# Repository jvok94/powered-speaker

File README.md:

# Connector Pin-outs

## SK1 (Power)

1. Ground
2. 24V AC 3A

## SK2 (Audio Input)

1. Left
2. Right
3. Ground

## SK3 (Volume Potentiometer)

1. Element (right contact)
2. Wiper
3. Element (left contact)

## SK4 (Speaker)

1. Live
2. Ground

## SK5 (LED)

1. Anode
2. Cathode

# Notes

* 2-pin connectors are Farnell order code 9632670 (https://uk.farnell.com/imo-precision-controls/20-101m-2/terminal-block-wire-to-brd-2pos/dp/9632670).
* 3-pin connectors are Farnell order code 9632689 (https://uk.farnell.com/imo-precision-controls/20-101m-3/terminal-block-wire-to-brd-3pos/dp/9632689).
* Power supply should be 24V AC (not DC), capable of at least 3A.
* Fuseholder F1 should be fitted with 3A time-lag fuse.
* To reduce hum, use shielded cable for input and potentiometer connections.

# Heatsinking

Q11 and Q12 should be attached to a heatsink with a maximum thermal resistance of 5K/W (lower is better). The tabs of the TO-220 packages are live, and so must be isolated from the heatsink using thermal pads. Mica or kapton work best, but SilPads are also acceptable. Either use nylon screws, or insulate the screws using suitable plastic bushings. A suitable kit containing both mica pads and bushings is available from Farnell, order code 520214 (https://uk.farnell.com/multicomp/mk3306/insulating-kit-mica-to-220/dp/520214). If using mica or kapton pads, coat them on both sides with a thin layer of thermal grease. Don't spread it too thick - you only need a very thin coating. Thermal grease is not required when using SilPads.

For everything you could possibly want to know about heatsinks (and more), a good read is http://sound.whsites.net/heatsinks.htm. Remember that when it comes to heatsinks, bigger is always better, and results in a cooler-running, more reliable amplifier

For optimum thermal stability, Q7 and Q9 should be in direct thermal contact with each other. Coat the back of one of the transistors with thermal grease, then use a cable tie around both transistor packages to hold them together. Doing the same with Q1 and Q2 will help to stop the DC offset from drifting with temperature.

# Assembly procedure

Solder all components to the PCB except for Q11 and Q12. You will need to fabricate some mounting to hold the PCB and heatsink together - do not rely on the transistor leads, as they or the solder joints will break. Once the PCB and heatsink are mounted, fit Q11 and Q12 to the board and bolt them to the heatsink. Solder the transistor leads last, after the packages have been mounted. This will reduce tension on the solder joints and prevent them from breaking. Using an ohmmeter, check to make sure there is no short circuit between the tabs of Q11 or Q12 and heatsink.

Adjust VR1 for to its minimum setting (1.2k resistance between base and emitter of Q7 - check this with a multimeter). Apply power but do not connect the audio input or speaker yet. Connect a voltmeter between the collectors of Q11 and Q12, then adjust VR1 until you measure 33mV - this corresponds to a quiescent current of 35mA. Leave the amplifier powered up for 30 minutes for the heatsink temperature to stabilise. After doing this, you are likely to find that the voltage has changed, so adjust VR1 again to bring it back to 33mV. Repeat this several times until the reading is stable. While doing this, monitor the heatsink temperature to ensure the amplifier does not overheat. The heatsink may get lukewarm but should not be hot.

Now connect the voltmeter across the speaker output. You may measure a small DC offset, but this should be less than 100mV. Anything larger than this indicates a construction error. Also check that there is no DC voltage on the input connector, to avoid damage to your audio source. Connect a speaker and audio source and listen to make sure that there is no distortion.

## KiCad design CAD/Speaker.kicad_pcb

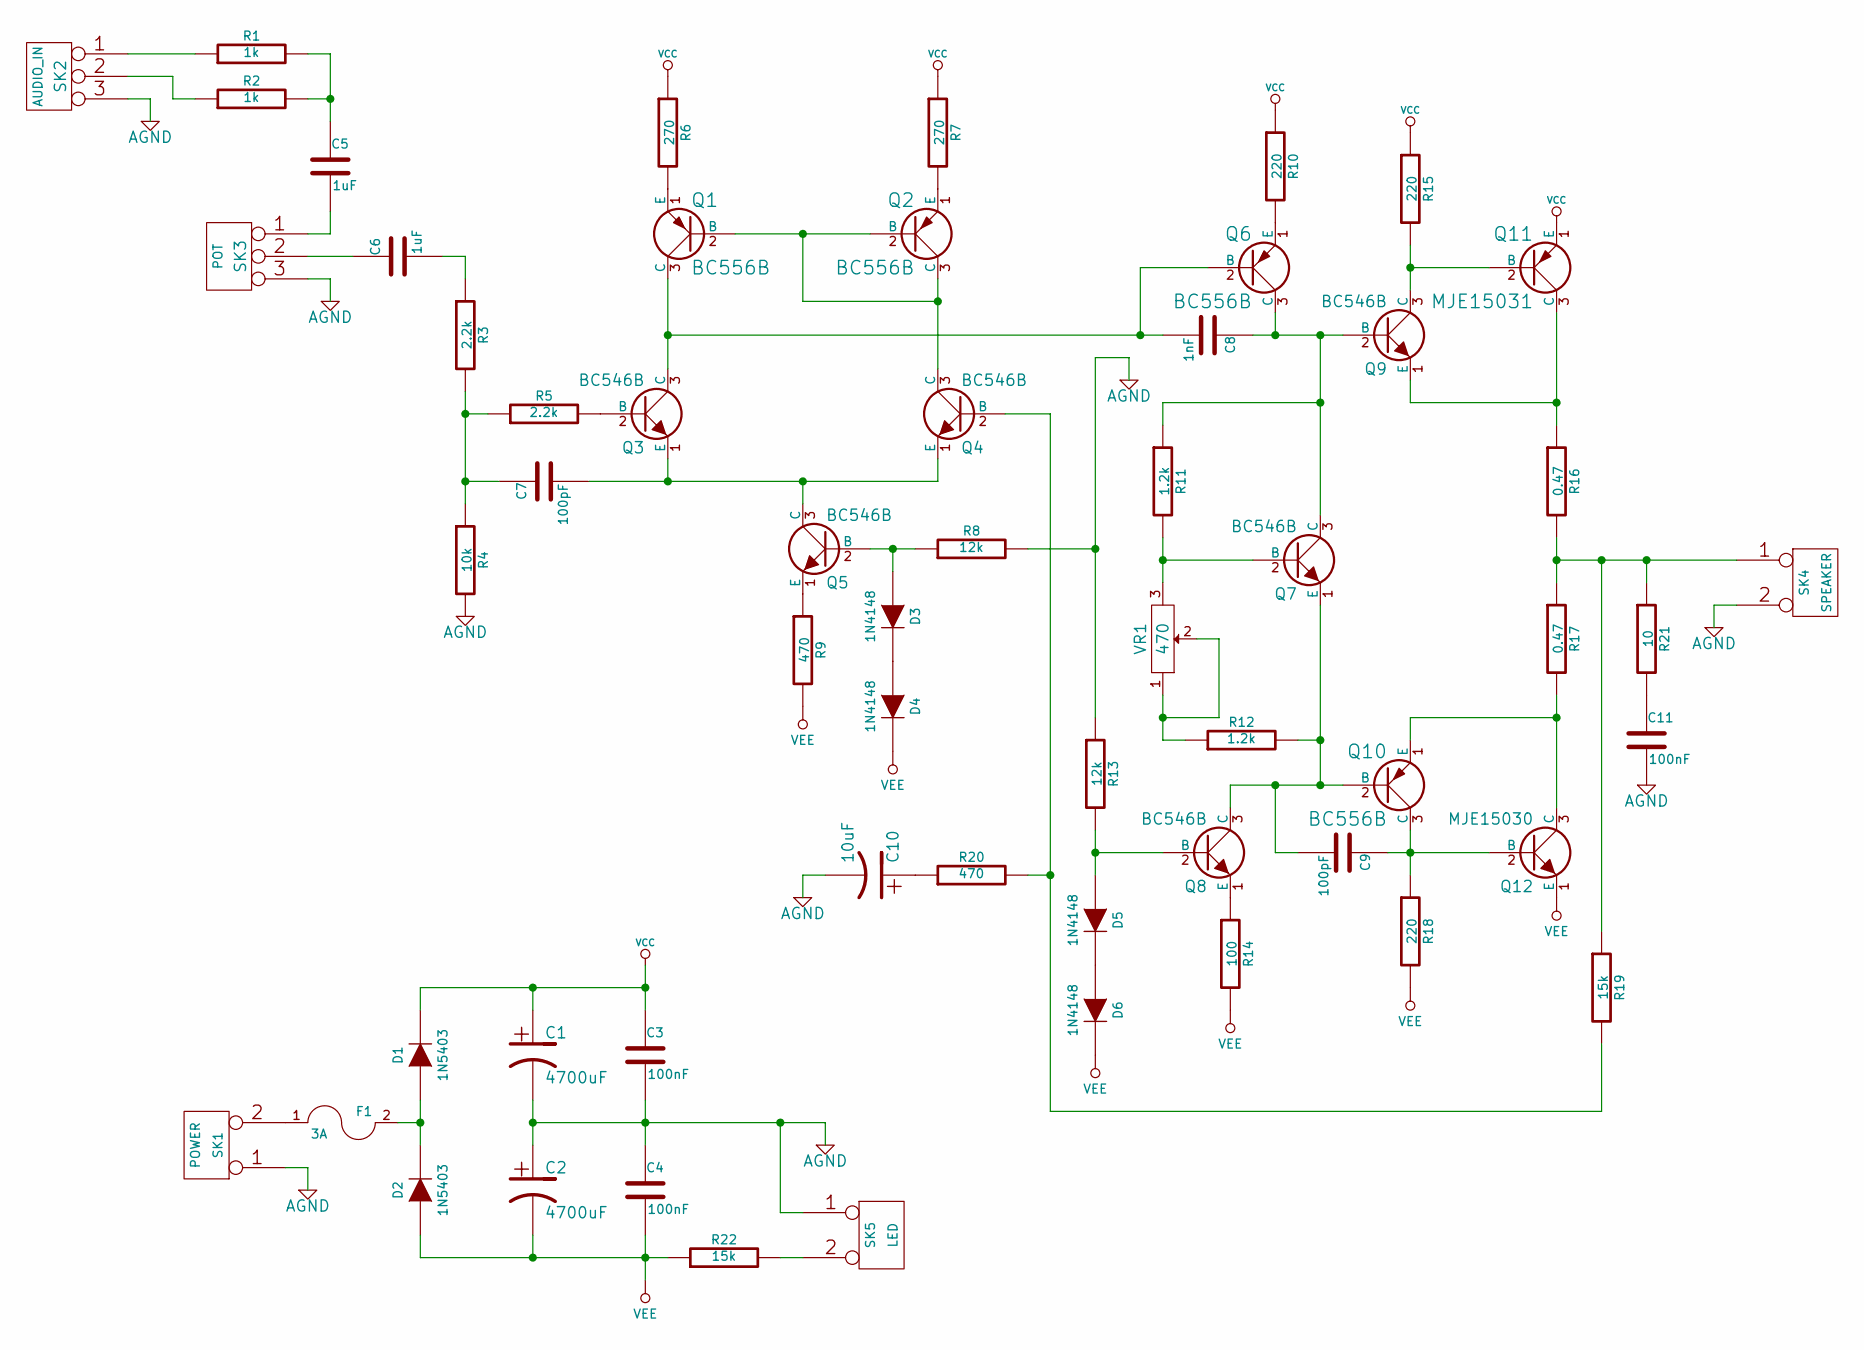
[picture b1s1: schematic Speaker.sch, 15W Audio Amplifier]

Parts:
C1, C2: 4700uF
C3, C4, C11: 100nF
C5, C6: 1uF
C7, C9: 100pF
C8: 1nF
C10: 10uF
D1, D2: 1N5403
D3, D4, D5, D6: 1N4148
F1: 3A
Q1, Q2, Q6, Q10: BC556B
Q3, Q4, Q5, Q7, Q8, Q9: BC546B
Q11: MJE15031
Q12: MJE15030
R1, R2: 1k
R3, R5: 2.2k
R4: 10k
R6, R7: 270
R8, R13: 12k
R9, R20: 470
R10, R15, R18: 220
R11, R12: 1.2k
R14: 100
R16, R17: 0.47
R19, R22: 15k
R21: 10
SK1: POWER
SK2: AUDIO_IN
SK3: POT
SK4: SPEAKER
SK5: LED
VR1: 470

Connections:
AGND: C1.2, C2.1, C3.2, C4.1, C10.2, C11.2, R4.2, R8.2, R13.1, SK1.1, SK2.3, SK3.3, SK4.2 (PM), SK5.1
unnamed: C7.1, R3.2, R4.1, R5.1
unnamed: C6.2, R3.1
unnamed: D5.2 (K), D6.1 (A)
unnamed: Q10.1 (E), Q12.3 (C), R17.2
unnamed: C9.1, Q10.3 (C), Q12.2 (B), R18.1
unnamed: Q9.1 (E), Q11.3 (C), R16.1
unnamed: C8.1, Q6.3 (C), Q7.3 (C), Q9.2 (B), R11.1
unnamed: Q7.2 (B), R11.2, VR1.3
unnamed: R1.1, SK2.1
unnamed: C5.1, R1.2, R2.2
unnamed: R2.1, SK2.2 (PM)
unnamed: Q9.3 (C), Q11.2 (B), R15.2
unnamed: C5.2, SK3.1
unnamed: D1.1 (A), D2.2 (K), F1.2
unnamed: F1.1, SK1.2 (PM)
unnamed: C6.1, SK3.2 (PM)
unnamed: R22.2, SK5.2 (PM)
unnamed: R12.1, VR1.1, VR1.2
unnamed: Q2.1 (E), R7.2
unnamed: Q1.1 (E), R6.2
unnamed: C8.2, Q1.3 (C), Q3.3 (C), Q6.2 (B)
unnamed: Q3.2 (B), R5.2
unnamed: D3.2 (K), D4.1 (A)
unnamed: C10.1, R20.1
unnamed: D3.1 (A), Q5.2 (B), R8.1
unnamed: Q5.1 (E), R9.1
unnamed: C7.2, Q3.1 (E), Q4.1 (E), Q5.3 (C)
unnamed: Q6.1 (E), R10.2
unnamed: C9.2, Q7.1 (E), Q8.3 (C), Q10.2 (B), R12.2
unnamed: Q8.1 (E), R14.1
unnamed: D5.1 (A), Q8.2 (B), R13.2
unnamed: R16.2, R17.1, R19.1, R21.1, SK4.1
unnamed: Q4.2 (B), R19.2, R20.2
unnamed: Q1.2 (B), Q2.2 (B), Q2.3 (C), Q4.3 (C)
unnamed: C11.1, R21.2
VCC: C1.1, C3.1, D1.2 (K), Q11.1 (E), R6.1, R7.1, R10.1, R15.1
VEE: C2.2, C4.2, D2.1 (A), D4.2 (K), D6.2 (K), Q12.1 (E), R9.2, R14.2, R18.2, R22.1

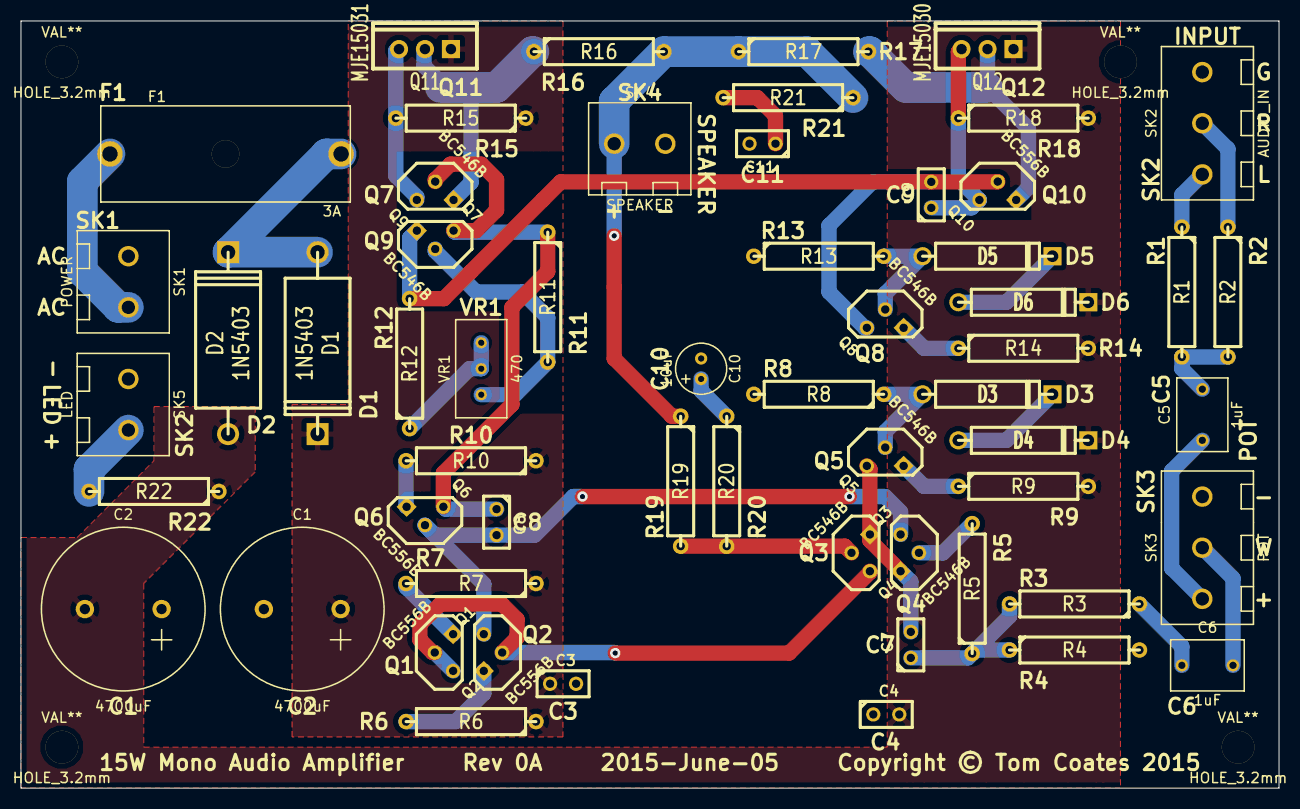
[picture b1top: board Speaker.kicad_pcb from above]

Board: 2 copper layers, 123.0 x 75.0 mm, 62 parts (0 on the bottom side), 38 nets.

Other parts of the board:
HOLE_3.2mm, HOLE_3.2mm#2, HOLE_3.2mm#3, HOLE_3.2mm#4: VAL**; HOLE_3.2mm

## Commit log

2018-10-07 Added readme
2018-10-07 Renamed readme

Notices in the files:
CAD/Speaker.kicad_pcb:
15W Mono Audio Amplifier Rev 0A 2015-June-05 Copyright © Tom Coates 2015
